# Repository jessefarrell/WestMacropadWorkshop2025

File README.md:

# WestMacropadWorkshop2025
This repository is intended to guide the user through the design of a small Macropad using KiCAD for schematic capture and PCB layout, fusion 360 for enclosure design, and QMK as the foundation for firmware. Students should be guided through the material by an instructor, there's not enough info for this repository to stand on its own (yet)

<em><strong>IMPORTANT NOTE</STRONG></em> - Bad Symbol
-
I made a <strong>mistake</strong> in the 0_west_symbol library provided during workshop #2. Please <u><strong>follow these steps to correct the NMOS symbol.</strong></u> If you do not complete these steps, pin 3 and 1 of the mosfet will be backwards.

1) Download the corrected symbol library
    - Go to <a href="https://github.com/jessefarrell/WestMacropadWorkshop2025/blob/main/kicad_libraries/0_west_symbols.kicad_sym">design_documents/0_west_symbols.kicad_sym</a> in the github repo and download the file
    - 
2) Replace <em>0_west_symbols.kicad_sym</em> in your project
    - Navigate to \WestMacropadWorkshop2025\kicad_libraries in your active project directory (not github)
    - Copy the file you downloaded in step 1 into kicad_libraries
    - Select <strong><u>replace the file in the destination</u></strong>
    - 

3) Sanity Check, & Update Symbol
    - If you've already placed the symbol, you'll have to tell KiCad to reload it
    - To do this <strong>*right-click*</strong> the symbol and go to "Update Symbol" The below window should pop up
    - Select the "Update symbols matching library identifier", and then "Select All" the fields... finally hit <strong>Update</strong>
    - 
    - Once the symbol is updated it should look like this (see below)... pin 3 on top and pin 1 on the bottom 
    - If you odn't see the pin numbers you can enable them using <strong>*right-click*</strong> -> Properties -> Show Pin Numbers
    - 

Workshop 3 - PCB Layout 
-
> PCB Workshop is primarily outlined in an external document. Several useful files for workshop 3 are stored in this repository.
- Basic Macropad Board Outline - <a href="https://github.com/jessefarrell/WestMacropadWorkshop2025/blob/main/design_documents/Basic_PCB_outline.dxf">/design_documents/Basic_PCB_outline.dxf</a>
    - The "dxf" file is a mechanical file that helps specify locations of critical components for the enclosure... such as key switches, the Pi Pico Development board, and screw holes
- Backup Reference Design - <a href="https://github.com/jessefarrell/WestMacropadWorkshop2025/releases/tag/Workshop%233-Start">Workshop#3 - Blank PCB</a>
    - Hopefully everyone is bringing in their own <em>custom</em> schematic from workshop 2... If not, students can always fall back on the reference design
    - Download the "source code (zip)" from the above link <strong>only if you need to</strong>  
    - 
- New Footprints - <a href="https://github.com/jessefarrell/WestMacropadWorkshop2025/tree/main/kicad_libraries/0_west_footprints.pretty">kicad_libraries/0_west_footprints.pretty</a>
    - I've added some Schneider and WEST logos to the 0_west_footprints library

Workshop 2 - Schematic
-
> Step by step instructions to be followed during the workshop.
1) Copy WestMacropadWorkshop2025 Workshop#2 to your local machine
    - We'll learn more about github & version control later :)
    - Download the "source code (zip)" from here the github repo -> <a href="https://github.com/jessefarrell/WestMacropadWorkshop2025/releases/tag/Workshop%232-start">WestMacropadWorkshop2025</a>
    - 
    - Extract the contents somewhere on your machine

2) Open **WestMacropadWorkshop2025/west_workshop_2025.kicad_pro**
    - This should automatically launch kicad 9
    - If not launch kicad 9 manually, and then go *File->Open Existing Project* and navigate to the above **kicad_pro** file
3) Double click **west_workshop_2025.kicad_sch** or launch the **Schematic Editor**
    - 

4) Your screen hopfully looks like this. You should be on Kicad v9 or higher.
    - 

5) Import WEST libaries (**Optional, but Useful for 3D Visualization**)
    - Symbols and footprints are already configured for the basic macropad
    - Only **the 3D models will be missing** by default
    - If you skip this step now, you may have to do it in workshop 3 or 4
    - First we'll need to import a third party plugin to get the 3d models for the switches
        - Launch the "Plugin and Content Manager"
        - 
        - Next navigate to "Repository", and "Libraries" shown below. Install the "Keyswitch Kicad Library", and then hit "Apply Pending Changes"
        - 
    - Next we're going to go back to the project homepage where we started and launch the **PCB Editor** then go **Preferences->Configure Paths...**
    - Add the following name and path
        - Name: KICAD_USER_3DMODEL_DIR
        - Path: ${KIPRJMOD}\3dmodels
    - 

6) Place your first symbol
    - Navigate to the **right toolbar** and click the ***"place symbols"*** (the sidways triangle button)
    - 
    - Your system will need to ***"load symbol libraries"*** the first time you do this... don't worry it only has to do this once
    - Find a random symbol and place it somewhere on the schematic
    - 🎉 First component placed!

7) Get familiar with the symbols we'll be using (place more symbols)
    - Key components have been organized into the **west_symbols libarary**, additional components related to the **advanced** macropad have not be pre configured
    - Raspberry pi pico **@west_symbols/RaspberryPi_Pico**
    - Key Switches **@west_symbols/Switch_Push**
    - Resistors **@west_symbols/Resistor**
    - LED **@west_symbols/LED**
    - MOSFET **@west_symbols/NMOS**

8) Create the diode key matrix discussed in the workshop
    - If you forget what that looks like, checkout the key matrix simulation using falstad ***WestMacropadWorkshop2025\design_documents\simulations***
    - Or take a look at the reference schematic ***WestMacropadWorkshop2025\design_documents\reference_schematic.pdf***
    - NOTE - If you're searching online you might see some schematics where the diodes are flipped compared to ours... this is because the **direction can be managed by QMK**, so long as **every diode is the same direction**

9) Create the backlight driver circuit
    - If you forget what that looks like, checkout the backlight driver simulation using falstad ***WestMacropadWorkshop2025\design_documents\simulations***
    - Or take a look at the reference schematic ***WestMacropadWorkshop2025\design_documents\reference_schematic.pdf***

10) Connect the backlight and matrix to the Pi Pico
    - So long as you connect them to a GPIO, it doesn't matter which specific GPIO you use
    - If you doing something more advanced such as driving a display, **BEWARE** not every GPIO is equivalent

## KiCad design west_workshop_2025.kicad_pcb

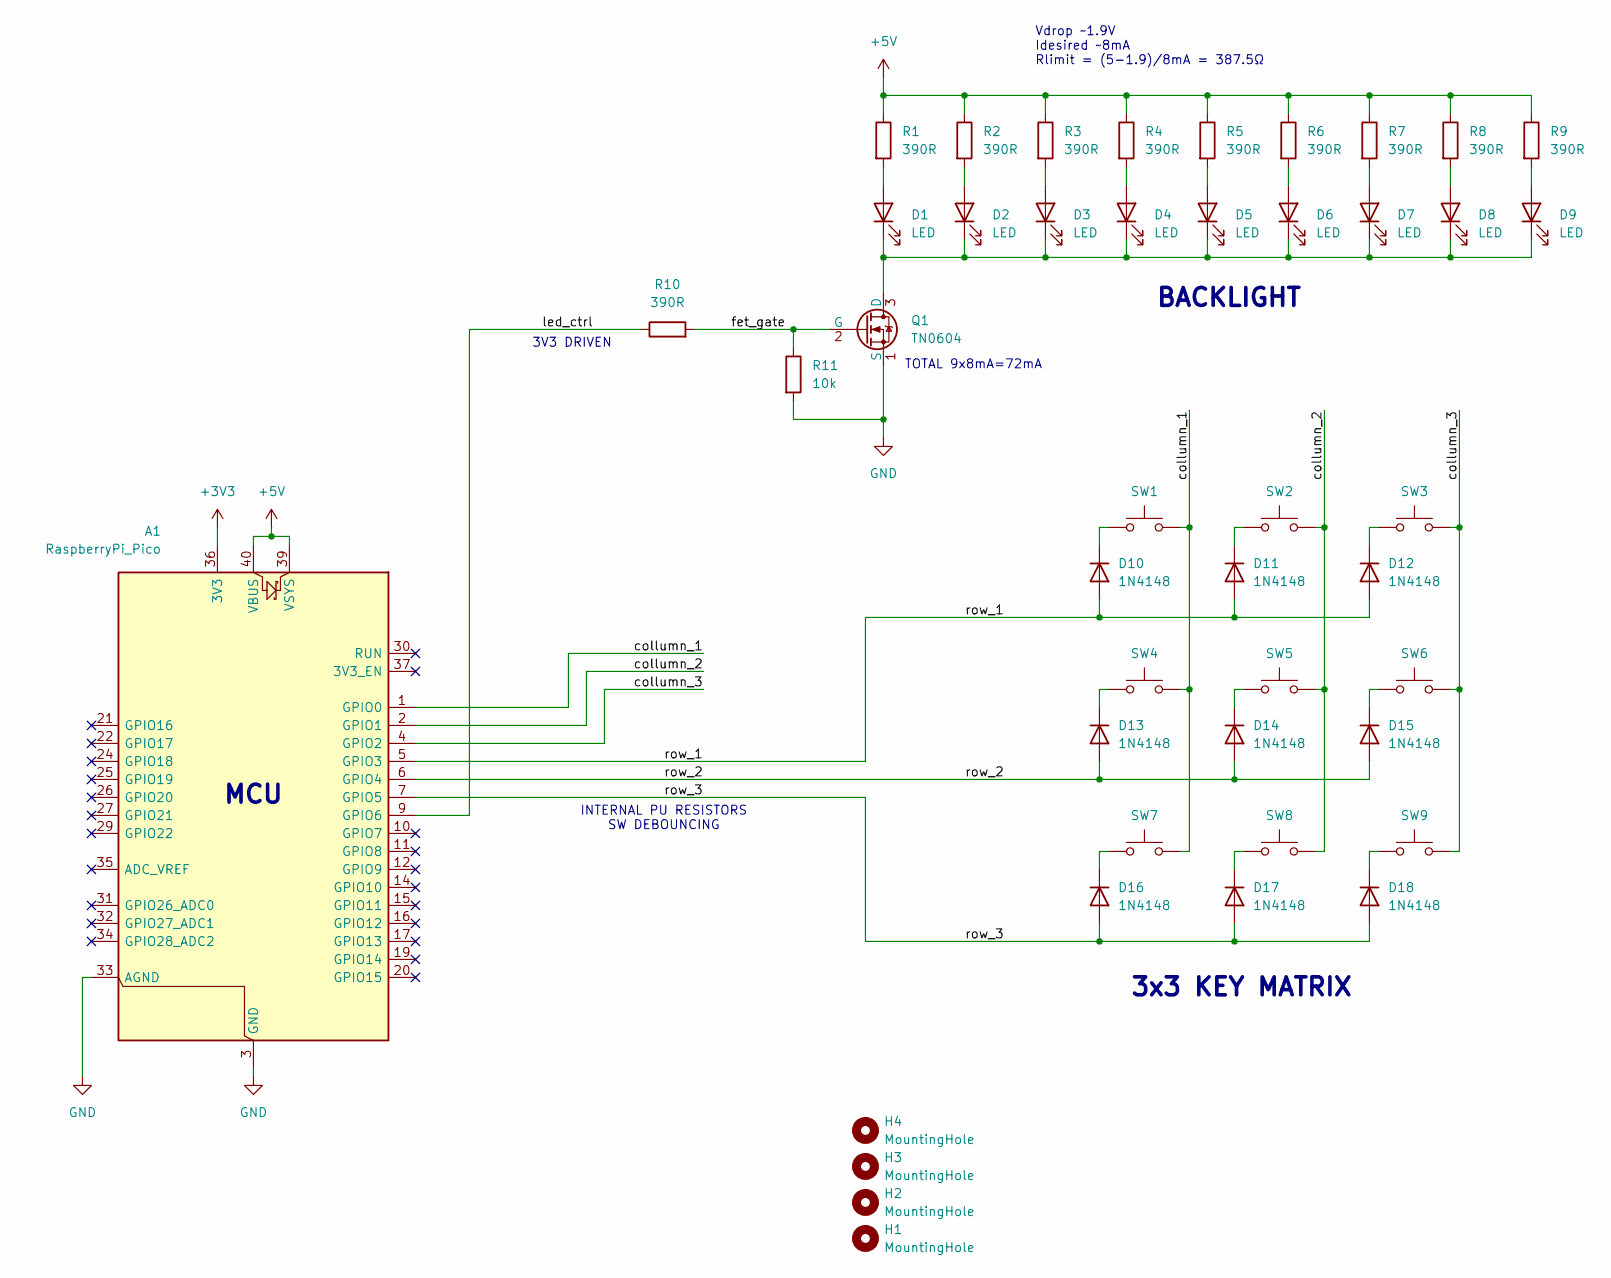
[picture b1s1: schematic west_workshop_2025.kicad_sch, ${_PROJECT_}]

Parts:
A1: RaspberryPi_Pico
D1, D2, D3, D4, D5, D6, D7, D8, D9: LED; Kingbright_WP914x
D10, D11, D12, D13, D14, D15, D16, D17, D18: 1N4148; D_DO-35_SOD27_P7.62mm_Horizontal
H1, H2, H3, H4: MountingHole; MountingHole_M2
Q1: TN0604; TO-92L_Inline
R1, R2, R3, R4, R5, R6, R7, R8, R9, R10: 390R; R_Axial_DIN0204_L3.6mm_D1.6mm_P5.08mm_Horizontal
R11: 10k; R_Axial_DIN0204_L3.6mm_D1.6mm_P5.08mm_Horizontal
SW1, SW2, SW3, SW4, SW5, SW6, SW7, SW8, SW9: switch_1.00u; SW_Cherry_MX_PCB_1.00u

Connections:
+3V3: A1.36 (3V3)
+5V: A1.39 (VSYS), A1.40 (VBUS), R1.1, R2.1, R3.1, R4.1, R5.1, R6.1, R7.1, R8.1, R9.1
/collumn_1: A1.1 (GPIO0), SW1.2, SW4.2, SW7.2
/collumn_2: A1.2 (GPIO1), SW2.2, SW5.2, SW8.2
/collumn_3: A1.4 (GPIO2), SW3.2, SW6.2, SW9.2
/fet_gate: Q1.2 (G), R10.2, R11.1
/led_ctrl: A1.9 (GPIO6), R10.1
/row_1: A1.5 (GPIO3), D10.2 (A), D11.2 (A), D12.2 (A)
/row_2: A1.6 (GPIO4), D13.2 (A), D14.2 (A), D15.2 (A)
/row_3: A1.7 (GPIO5), D16.2 (A), D17.2 (A), D18.2 (A)
GND: A1.3 (GND), A1.8 (GND), A1.13 (GND), A1.18 (GND), A1.23 (GND), A1.28 (GND), A1.33 (AGND), A1.38 (GND), Q1.1 (S), R11.2
unnamed: D1.2 (A), R1.2
unnamed: D1.1 (K), D2.1 (K), D3.1 (K), D4.1 (K), D5.1 (K), D6.1 (K), D7.1 (K), D8.1 (K), D9.1 (K), Q1.3 (D)
unnamed: D2.2 (A), R2.2
unnamed: D3.2 (A), R3.2
unnamed: D4.2 (A), R4.2
unnamed: D5.2 (A), R5.2
unnamed: D6.2 (A), R6.2
unnamed: D7.2 (A), R7.2
unnamed: D8.2 (A), R8.2
unnamed: D9.2 (A), R9.2
unnamed: D10.1 (K), SW1.1
unnamed: D11.1 (K), SW2.1
unnamed: D12.1 (K), SW3.1
unnamed: D13.1 (K), SW4.1
unnamed: D14.1 (K), SW5.1
unnamed: D15.1 (K), SW6.1
unnamed: D16.1 (K), SW7.1
unnamed: D17.1 (K), SW8.1
unnamed: D18.1 (K), SW9.1

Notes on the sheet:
MCU
3V3 DRIVEN
3x3 KEY MATRIX
BACKLIGHT
TOTAL 9x8mA=72mA
Vdrop ~1.9V Idesired ~8mA Rlimit = (5-1.9)/8mA = 387.5Ω
INTERNAL PU RESISTORS SW DEBOUNCING

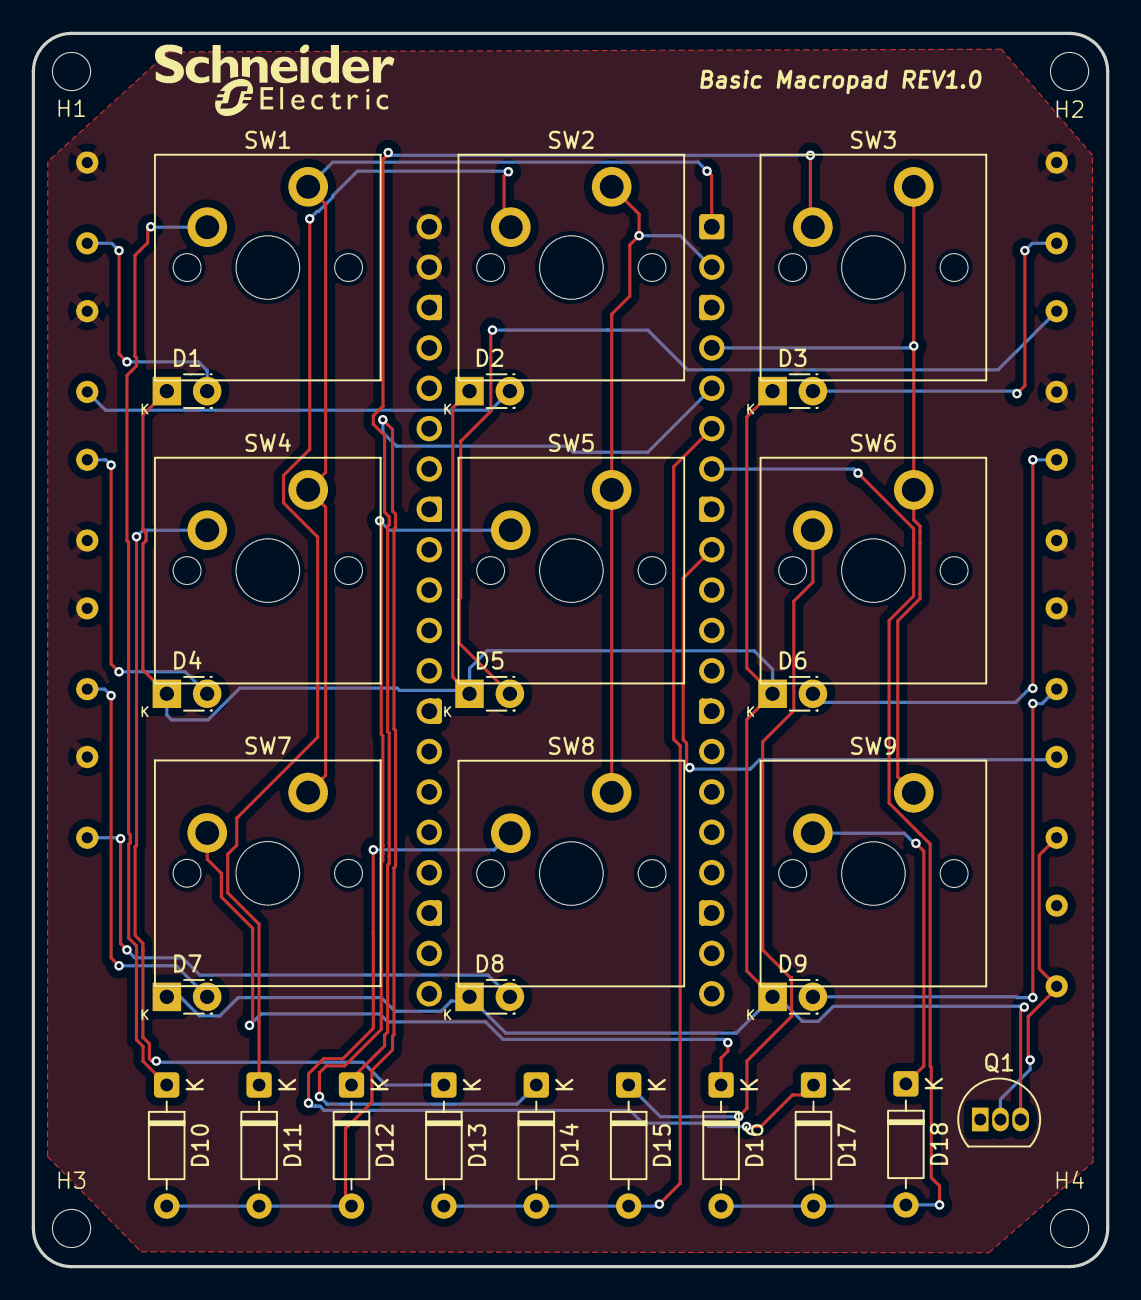
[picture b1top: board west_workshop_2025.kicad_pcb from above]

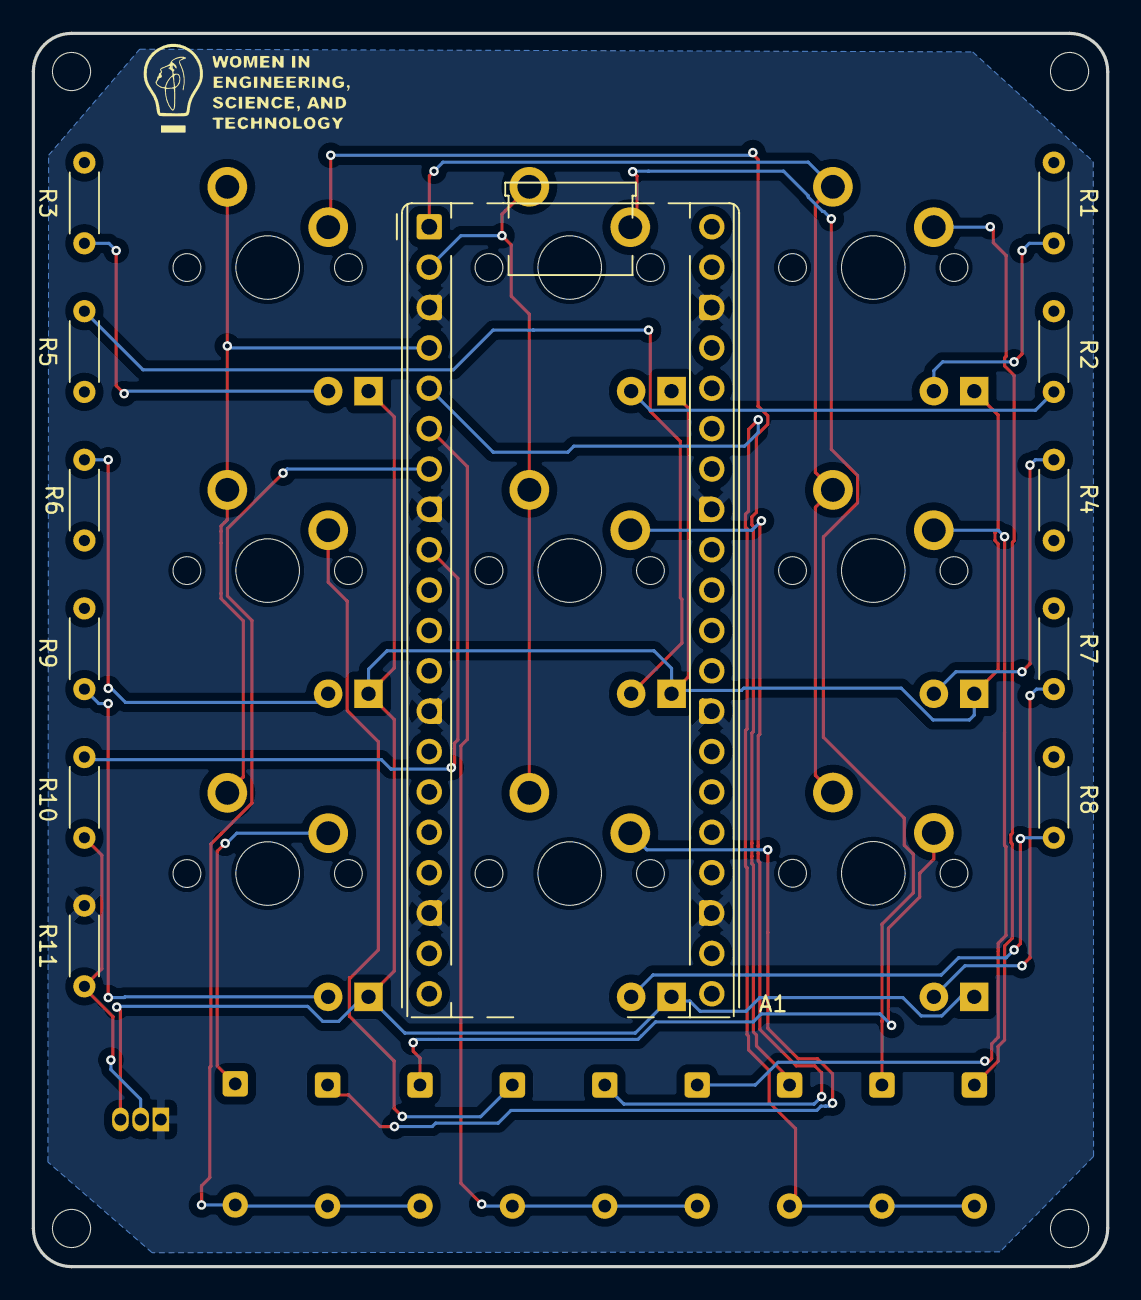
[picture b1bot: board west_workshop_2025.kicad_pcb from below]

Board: 4 copper layers, 67.6 x 77.6 mm, 44 parts (12 on the bottom side), 29 nets.

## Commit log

2025-05-16 Add core material
    > Lots of background documentation added
    > Project configured for JLCPCB (ie. DRC)
    > Placed mounting holes and JLC order number on schematic just so we have a starting point
2025-05-16 Various documentation updates
    > Add simulations
    > Change project name
    > Lots of readme
2025-05-20 Various Updates
2025-05-21 Changed footprint library: global --> project
    > this makes it so students don't need to import libraries anymore
    > Path info is stored in the fp/sym-lib-table files
2025-05-21 Cleaned schematic --blank--
2025-05-21 Formatting images
2025-05-21 Make 3D models paths relative
2025-05-21 Added more notes, Removed JLC footprint TP
2025-05-21 Add diode symbol
2025-05-21 Add new images
2025-05-21 Add instructions - how to download repo
2025-05-21 Schematic Done - Ready for layout
2025-05-21 Revert Change - Release issues
2025-05-21 Update link
2025-05-21 Schematic Done
2025-05-21 Update west_workshop_2025.kicad_sch
    - Add Text
2025-05-21 Add more design documents
2025-05-28 Correct NMOS pin numbering - IMPORTANT!!!!
2025-05-28 Add =SE= logo and images
2025-05-28 Create =SE= & WEST Logo Footprint
2025-05-28 Add Basic Macropad PCB Outline
2025-05-28 Minor Cleanup + NMOS Fix Applied
2025-05-28 Clean PCB.
2025-05-28 Finished PCB
2025-05-28 Add reference to releases
2025-05-28 Add layout document for Workshop#3
2025-05-28 Fix formatting
2025-05-28 Replace and rename document
    - Grammar fixes
2025-05-29 Add info to symbol fix
2025-05-30 Add and move images
2025-05-30 Update info on Symbol Correction
2025-05-30 Added advanced keypad Fusion model
2025-05-30 Moved fusion models out of 3dmodel folder
2025-06-02 Added info to rotary encoder and display
2025-06-02 Add footprint info for display header
2025-06-03 Updated advanced case design
    There was an issue with the .f3z in Fusion online. Had to redesign the part so it could be exported as an f3d (not an assembly).
2025-06-03 Add better notes for the 3d model linking
    Step 5 on the workshop 2
2025-06-10 New images for documentation
2025-06-10 Remove useless files
2025-06-10 Add readme for firmware/software workshop
2025-06-11 Update readme.md
    changes to LED backlight section
2025-06-12 Add FW used for demo
2025-06-13 Add onekey docs and start numbering steps
    > Needs a reformat pretty bad...
    > Pull all the compile instructions to a single point
2025-06-13 Update readme.md
    minor grammar...pesky "your" -> "you're"
2025-06-14 FW files for basic ref design
    FW files for num pad only, and for num pad plus backlight on a new layer.
2025-06-23 single key with autoshift
2025-06-24 removed info.json - not needed
2025-06-25 Prep for Software Workshop
2025-06-25 Rename folder, remove backlight from iteration 1
    > Originally in the "start" folder there was some setup for the backlight
    > We decided to remove this setup to better align with the iteration 1 / 2 template
2025-06-25 Update wording
2025-06-25 Align iteration 1/2 for basic macropad
2025-06-25 Readme cleanup
2025-06-25 Tested single key and basic on laptop, cleanup text
2025-07-01 Update documentation (RGB, OLED)
